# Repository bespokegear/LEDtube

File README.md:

# LEDtube
Arduino code for Sound rsponsive LED light unit.

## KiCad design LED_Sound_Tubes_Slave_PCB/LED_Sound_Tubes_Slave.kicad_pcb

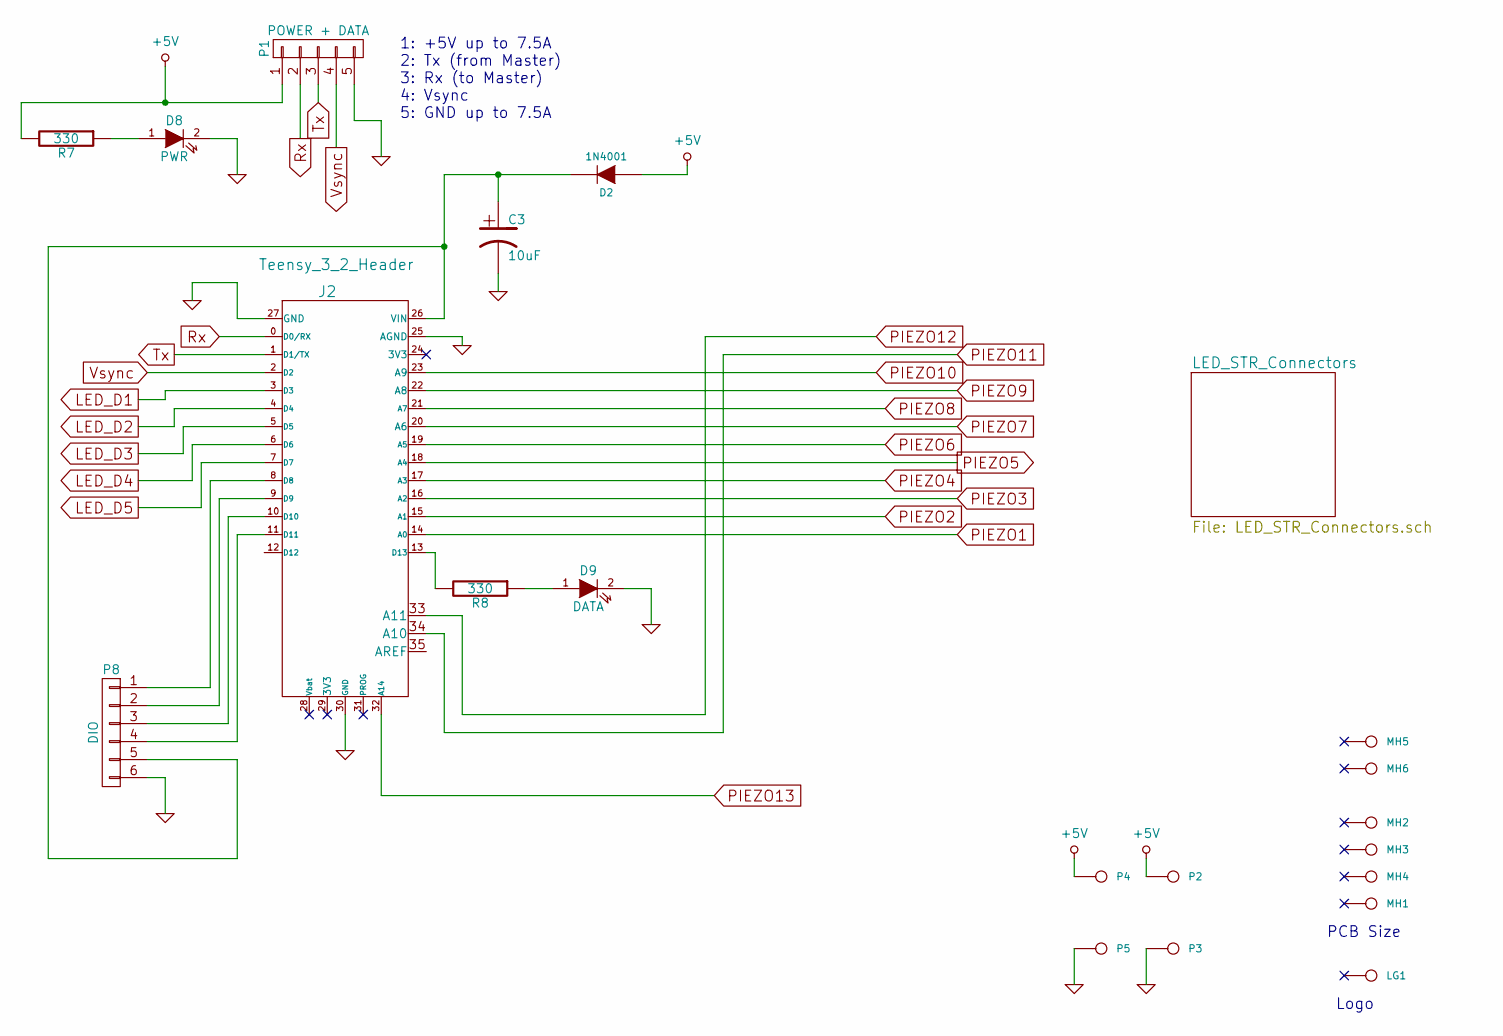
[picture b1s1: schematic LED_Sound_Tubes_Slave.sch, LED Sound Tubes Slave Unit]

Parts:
C3: 10uF; C2V8_V; Manufacturer Part No Value
D2: 1N4001; TH_Diode_1
D8: PWR; LED-5MM_large_pads
D9: DATA; LED-5MM_large_pads
J2: Teensy_3_2_Header; TH_Teensy-3.1
LG1: CONN_1; reinnovation_logo_15mm
MH1, MH2, MH3, MH4, MH5, MH6: CONN_1; 3mm_hole
P1: POWER + DATA; CONN_TH_5W_SIL_5_08
P2, P4: +5V; CONN_3mm_Terminal; Manufacturer Part No Value
P3, P5: 0V; CONN_3mm_Terminal; Manufacturer Part No Value
P8: DIO; CONN_TH_6W_MK
R7, R8: 330; TH_Resistor_1

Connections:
+5V: D2.1 (A), P1.1, P2.1, P4.1, R7.2; also elsewhere on the board
LED_D1: J2.3 (D3); also elsewhere on the board
LED_D2: J2.4 (D4); also elsewhere on the board
LED_D3: J2.5 (D5); also elsewhere on the board
LED_D4: J2.6 (D6); also elsewhere on the board
LED_D5: J2.7 (D7); also elsewhere on the board
unnamed: C3.1, D2.2 (K), J2.26 (VIN), P8.5
unnamed: D8.1 (A), R7.1
unnamed: D9.1 (A), R8.1
unnamed: J2.8 (D8), P8.1
unnamed: J2.9 (D9), P8.2
unnamed: J2.10 (D10), P8.3
unnamed: J2.11 (D11), P8.4
unnamed: J2.13 (D13), R8.2
PIEZO1: J2.14 (A0); also elsewhere on the board
PIEZO2: J2.15 (A1); also elsewhere on the board
PIEZO3: J2.16 (A2); also elsewhere on the board
PIEZO4: J2.17 (A3); also elsewhere on the board
PIEZO5: J2.18 (A4); also elsewhere on the board
PIEZO6: J2.19 (A5); also elsewhere on the board
PIEZO7: J2.20 (A6); also elsewhere on the board
PIEZO8: J2.21 (A7); also elsewhere on the board
PIEZO9: J2.22 (A8); also elsewhere on the board
PIEZO10: J2.23 (A9); also elsewhere on the board
PIEZO11: J2.34 (A10); also elsewhere on the board
PIEZO12: J2.33 (A11); also elsewhere on the board
PIEZO13: J2.32 (A14); also elsewhere on the board
Rx: J2.0 (D0/RX), P1.2
Tx: J2.1 (D1/TX), P1.3
Vsync: J2.2 (D2), P1.4

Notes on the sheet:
PCB Size
Logo
1: +5V up to 7.5A 2: Tx (from Master) 3: Rx (to Master) 4: Vsync 5: GND up to 7.5A

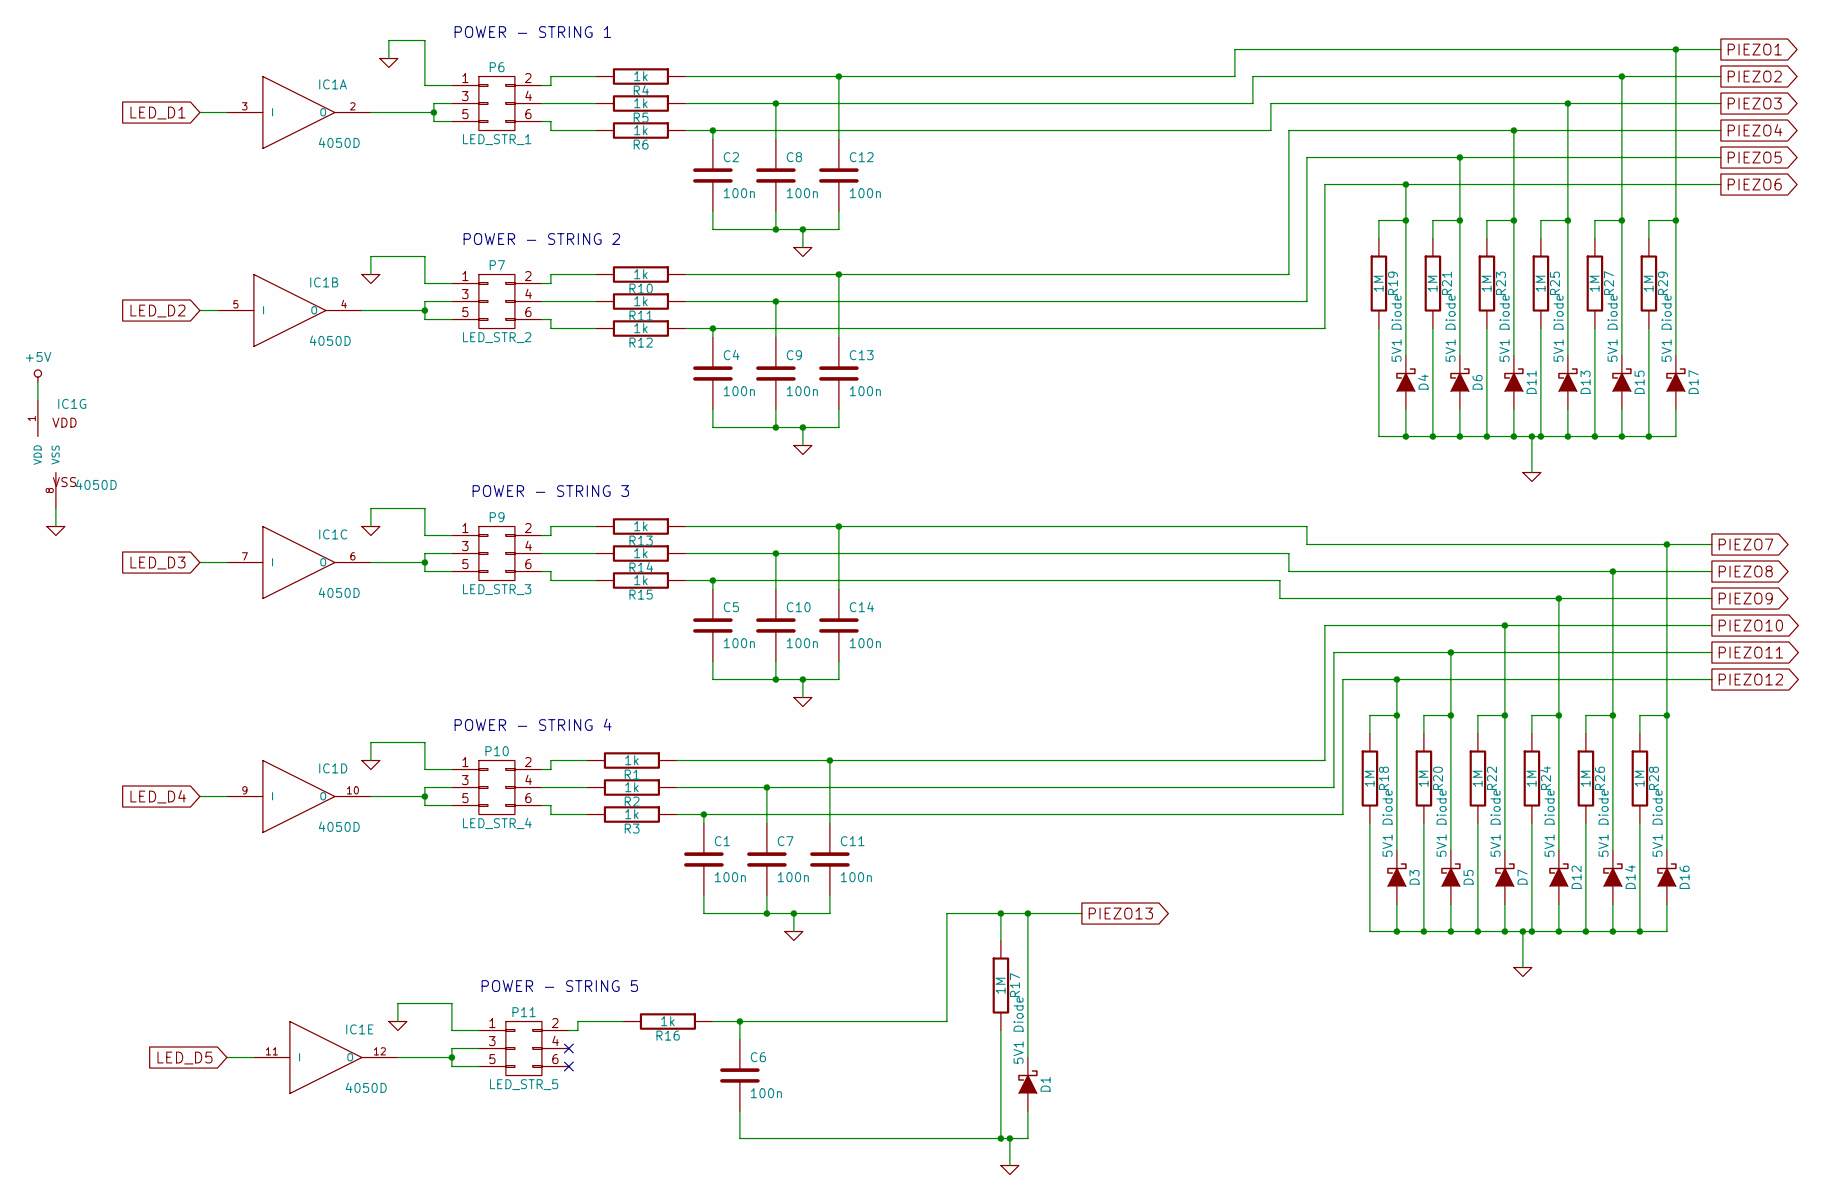
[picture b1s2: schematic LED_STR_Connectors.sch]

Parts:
C1, C2, C4, C5, C6, C7, C8, C9, C10, C11, C12, C13, C14: 100n; C1_wide_lg_pad; Manufacturer Part No Value
D1, D3, D4, D5, D6, D7, D11, D12, D13, D14, D15, D16, D17: 5V1 Diode; TH_Diode_3
IC1: 4050D; DIP-16__NARROW
P6: LED_STR_1; IDC_Header_6W_2.54
P7: LED_STR_2; IDC_Header_6W_2.54
P9: LED_STR_3; IDC_Header_6W_2.54
P10: LED_STR_4; IDC_Header_6W_2.54
P11: LED_STR_5; IDC_Header_6W_2.54
R1, R2, R3, R4, R5, R6, R10, R11, R12, R13, R14, R15, R16: 1k; TH_Resistor_1
R17, R18, R19, R20, R21, R22, R23, R24, R25, R26, R27, R28, R29: 1M; TH_Resistor_1

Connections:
+5V: IC1.1 (VDD); also elsewhere on the board
LED_D1: IC1.3 (I); also elsewhere on the board
LED_D2: IC1.5 (I); also elsewhere on the board
LED_D3: IC1.7 (I); also elsewhere on the board
LED_D4: IC1.9 (I); also elsewhere on the board
LED_D5: IC1.11 (I); also elsewhere on the board
unnamed: IC1.2 (O), P6.3, P6.5
unnamed: IC1.4 (O), P7.3, P7.5
unnamed: IC1.6 (O), P9.3, P9.5
unnamed: IC1.10 (O), P10.3, P10.5
unnamed: IC1.12 (O), P11.3, P11.5
unnamed: P6.2, R4.2
unnamed: P6.4, R5.2
unnamed: P6.6, R6.2
unnamed: P7.2, R10.2
unnamed: P7.4, R11.2
unnamed: P7.6, R12.2
unnamed: P9.2, R13.2
unnamed: P9.4, R14.2
unnamed: P9.6, R15.2
unnamed: P10.2, R1.2
unnamed: P10.4, R2.2
unnamed: P10.6, R3.2
unnamed: P11.2, R16.2
PIEZO1: C12.1, D17.1 (K), R4.1, R29.1; also elsewhere on the board
PIEZO2: C8.1, D15.1 (K), R5.1, R27.1; also elsewhere on the board
PIEZO3: C2.1, D13.1 (K), R6.1, R25.1; also elsewhere on the board
PIEZO4: C13.1, D11.1 (K), R10.1, R23.1; also elsewhere on the board
PIEZO5: C9.1, D6.1 (K), R11.1, R21.1; also elsewhere on the board
PIEZO6: C4.1, D4.1 (K), R12.1, R19.1; also elsewhere on the board
PIEZO7: C14.1, D16.1 (K), R13.1, R28.1; also elsewhere on the board
PIEZO8: C10.1, D14.1 (K), R14.1, R26.1; also elsewhere on the board
PIEZO9: C5.1, D12.1 (K), R15.1, R24.1; also elsewhere on the board
PIEZO10: C11.1, D7.1 (K), R1.1, R22.1; also elsewhere on the board
PIEZO11: C7.1, D5.1 (K), R2.1, R20.1; also elsewhere on the board
PIEZO12: C1.1, D3.1 (K), R3.1, R18.1; also elsewhere on the board
PIEZO13: C6.1, D1.1 (K), R16.1, R17.1; also elsewhere on the board

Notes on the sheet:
POWER - STRING 2
POWER - STRING 1
POWER - STRING 3
POWER - STRING 4
POWER - STRING 5

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
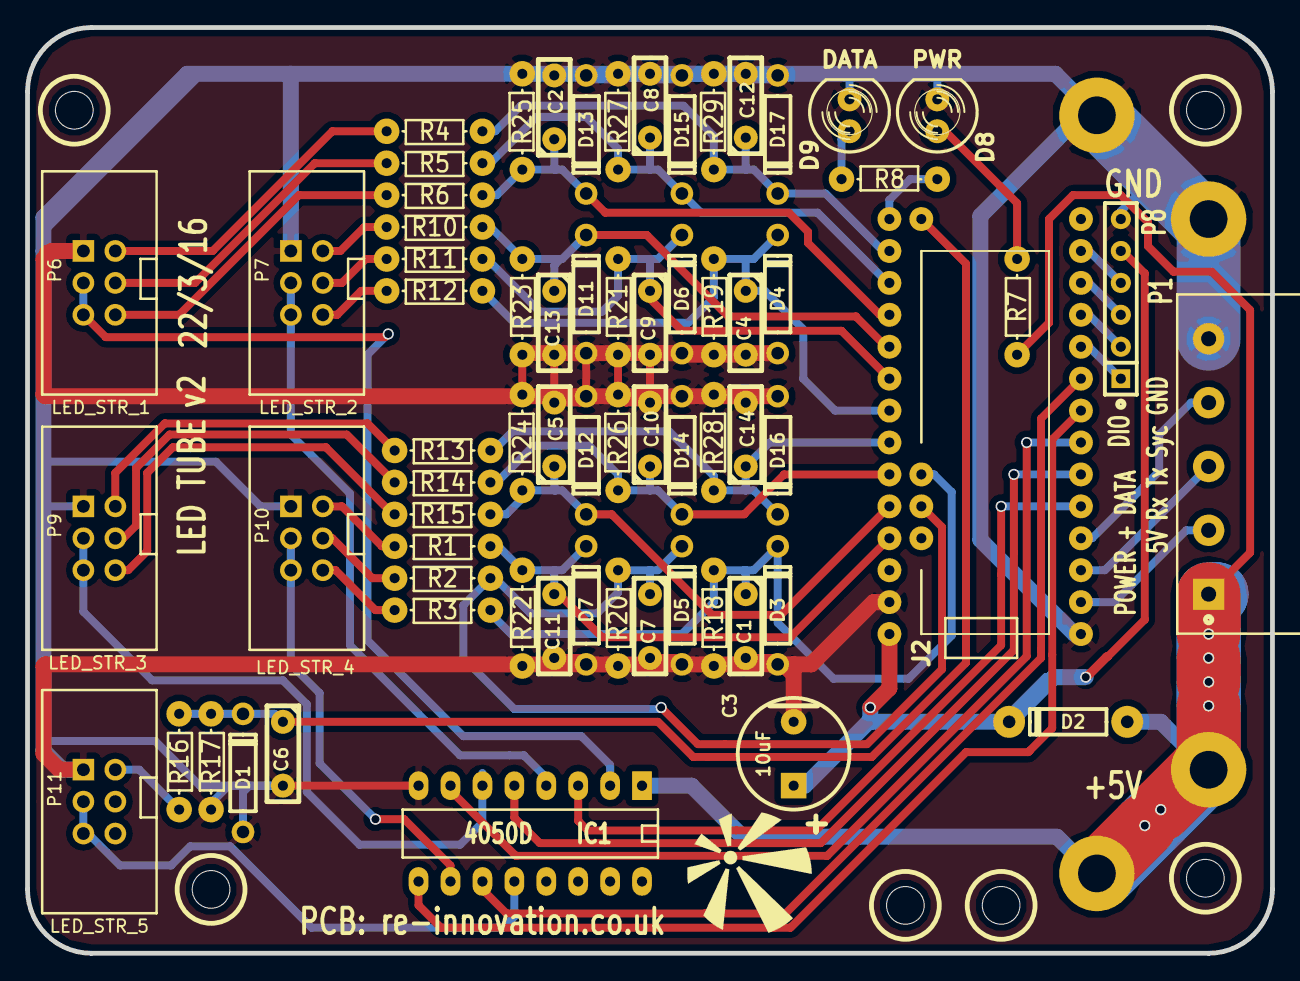
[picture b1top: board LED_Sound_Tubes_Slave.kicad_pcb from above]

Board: 2 copper layers, 99.1 x 73.7 mm, 78 parts (0 on the bottom side), 49 nets.

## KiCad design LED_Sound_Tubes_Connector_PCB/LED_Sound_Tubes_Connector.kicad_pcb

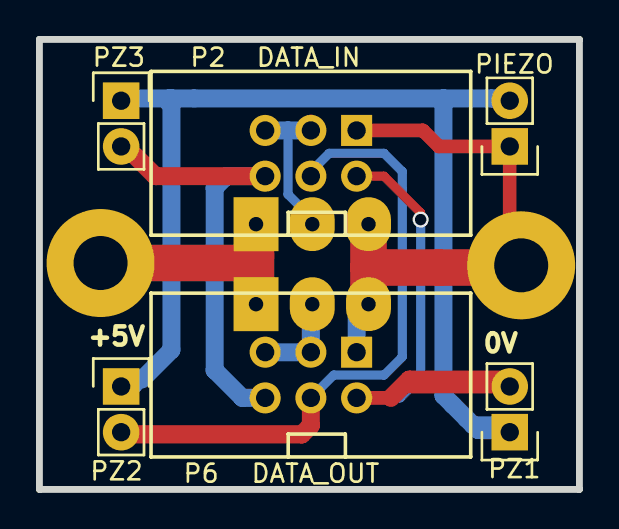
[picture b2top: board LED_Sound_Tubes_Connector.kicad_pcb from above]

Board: 2 copper layers, 30.0 x 25.0 mm, 10 parts (0 on the bottom side), 8 nets.

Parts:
P1: LED_OUT; CONN_LED_Strip
P2: DATA_OUT; IDC_Header_6W_2.54
P3: PIEZO; Pin_Header_Straight_1x02
P4: PZ1; Pin_Header_Straight_1x02
P5: LED_IN; CONN_LED_Strip
P6: DATA_IN; IDC_Header_6W_2.54
P7: PZ2; Pin_Header_Straight_1x02
P8: PZ3; Pin_Header_Straight_1x02
P9: 0V; CONN_3mm_Terminal
P10: +5V; CONN_3mm_Terminal

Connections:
+5V: P1.1, P5.1, P10.1
GND: P1.3, P2.1, P3.1, P5.3, P6.1, P9.1
unnamed: P1.2, P2.3, P2.5
unnamed: P2.2, P4.2, P6.2
unnamed: P2.4, P6.4, P7.2
unnamed: P2.6, P6.6, P8.2
unnamed: P3.2, P4.1, P7.1, P8.1
unnamed: P5.2, P6.3, P6.5

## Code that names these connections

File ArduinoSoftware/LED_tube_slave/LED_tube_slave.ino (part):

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

// These constants won't change.  They're used to give names to the pins used:
const int piezo1 = A0; 
const int piezo2 = A1; 
const int piezo3 = A2;  
const int piezo4 = A3;
const int piezo5 = A4;  
const int piezo6 = A5;  

const int LEDperPixel = 2; // (50 max) This is the number of LEDs that make up a pixel unit
const int pixelsPerSlave = 4;  // Number of pixels from one slave unit
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
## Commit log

2015-12-16 Initial commit
    First version of Arduino code. Controls lights via Serial commands
2016-03-22 PCB redesign
    Use Teensy only
2016-03-23 New PCB with filters
    Added filters. Total redesign of PCB
